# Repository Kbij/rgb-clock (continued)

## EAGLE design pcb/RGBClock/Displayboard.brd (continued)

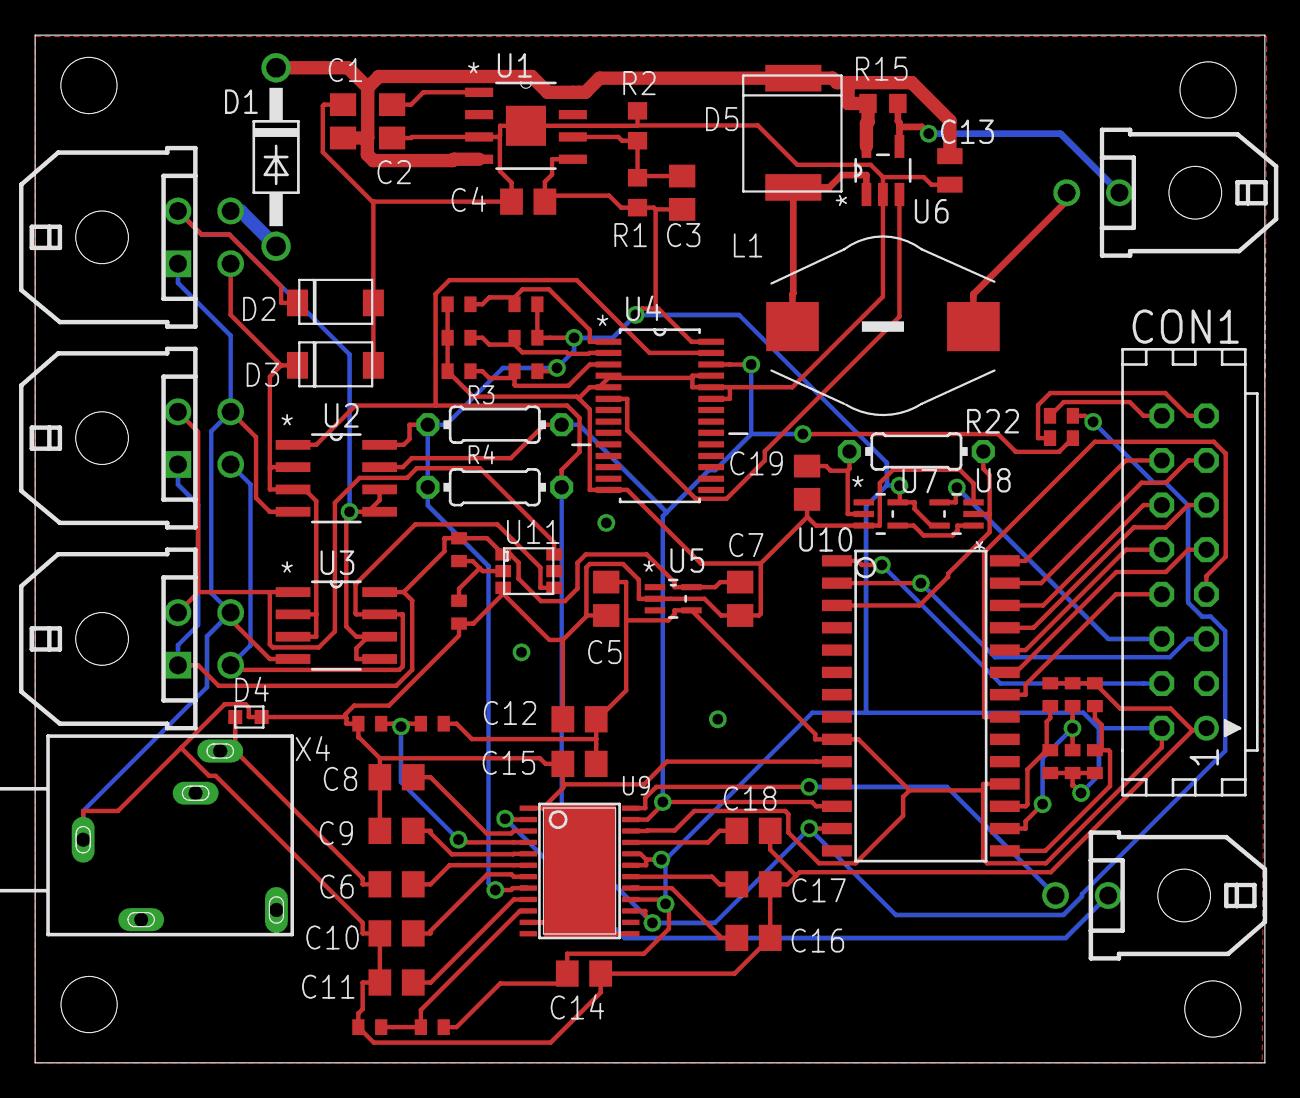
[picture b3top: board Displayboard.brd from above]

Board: 2 copper layers, 70.0 x 58.5 mm, 69 parts (0 on the bottom side), 53 nets.

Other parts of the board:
R27: A1-1; R0402
R28: A1-0; R0402
U9: TPA0172-HTSSOP24; HT-TSSOP-24
U10: MCP23017SO; SO28W
U11: TSL2561; TMB-6

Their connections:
+3V3: R27.2, U11.1; also elsewhere on the board
+5V: U9.8, U9.16, U9.19, U9.20, U9.22, U10.9, U10.18; also elsewhere on the board
D0: U10.21; also elsewhere on the board
D1: U10.22; also elsewhere on the board
D2: U10.23; also elsewhere on the board
D3: U10.24; also elsewhere on the board
D4: U10.25; also elsewhere on the board
D5: U10.26; also elsewhere on the board
D6: U10.27; also elsewhere on the board
D7: U10.28; also elsewhere on the board
GND: R28.1, U9.1, U9.11, U9.13, U9.HEATSINK, U10.10, U11.3; also elsewhere on the board
unnamed 13: U10.3; also elsewhere on the board
unnamed 14: U9.17; also elsewhere on the board
unnamed 15: U9.18; also elsewhere on the board
unnamed 17: U11.6; also elsewhere on the board
unnamed 19: U11.4; also elsewhere on the board
unnamed 21: U9.24; also elsewhere on the board
unnamed 22: U9.2; also elsewhere on the board
unnamed 23: U9.6; also elsewhere on the board
unnamed 24: U9.9; also elsewhere on the board
unnamed 25: U9.7; also elsewhere on the board
unnamed 26: U9.5; also elsewhere on the board
unnamed 27: U9.3; also elsewhere on the board
unnamed 28: U10.16; also elsewhere on the board
unnamed 29: U10.15; also elsewhere on the board
unnamed 31: U10.17; also elsewhere on the board
unnamed 33: U9.21; also elsewhere on the board
unnamed: R27.1, R28.2, U11.2
unnamed 44: U9.4; also elsewhere on the board
unnamed 45: U9.10; also elsewhere on the board
RS: U10.1; also elsewhere on the board
RW: U10.2; also elsewhere on the board
SCL: U9.23, U10.12; also elsewhere on the board
SDA: U9.15, U10.13; also elsewhere on the board

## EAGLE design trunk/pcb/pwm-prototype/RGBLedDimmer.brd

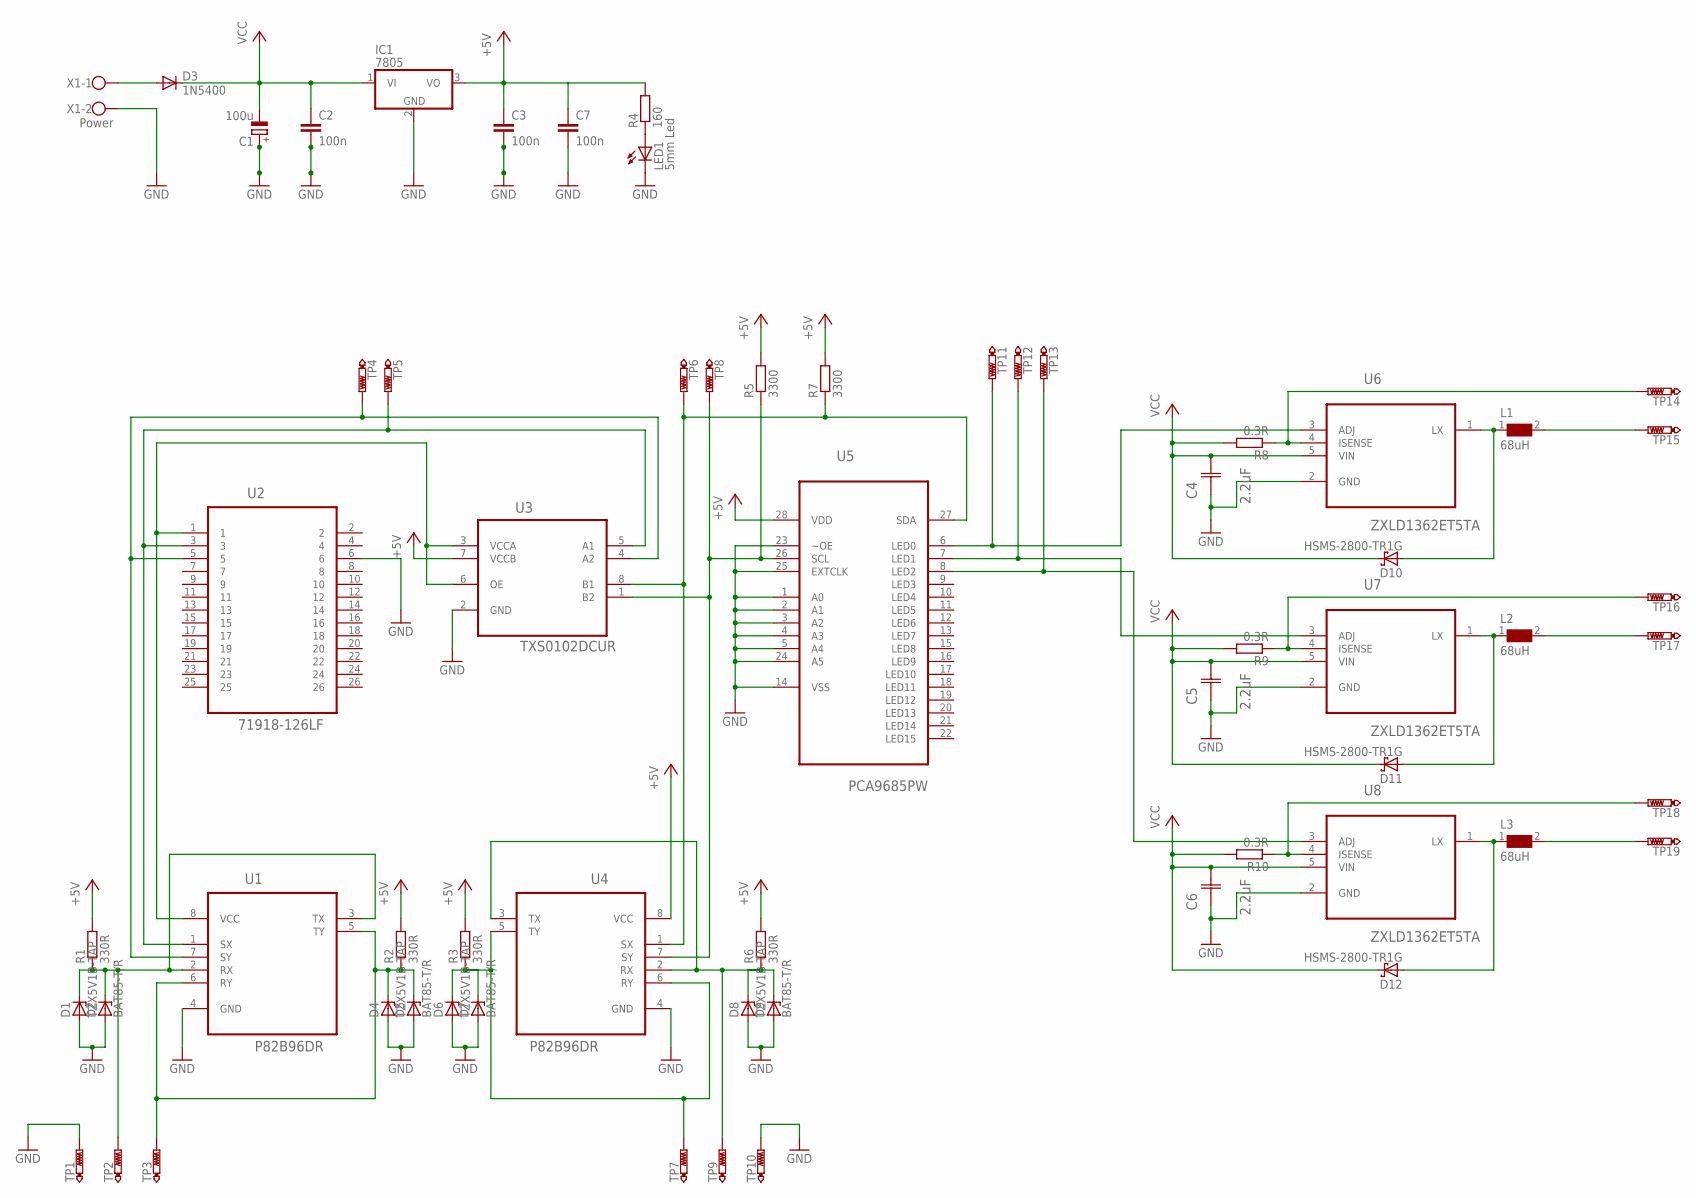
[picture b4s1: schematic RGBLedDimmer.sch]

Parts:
C1: 100u; E3,5-8
C2, C3, C7: 100n; C025_050-025X075
C4, C5, C6: 2.2uF; CAPC2013X152N
D1, D4, D6, D8: TZX5V1B-TAP; DO34Z7
D2, D5, D7, D9: BAT85-T/R; DO34Z7
D3: 1N5400; DO201-15
D10, D11, D12: HSMS-2800-TR1G; SOT23
IC1: 7805; TO220V
L1, L2, L3: 68uH; L
LED1: 5mm Led; LED5MM
R1, R2, R3, R6: 330R; 0204/7
R4: 160; 0204/7
R5, R7: 3300; 0204/7
R8, R9, R10: 0.3R; R0603
TP1, TP2, TP3, TP4, TP5, TP6, TP7, TP8, TP9, TP10, TP11, TP12, TP13, TP14, TP15, TP16, TP17, TP18, TP19: PTR1PAD1-13; P1-13
U1, U4: P82B96DR; SOIC127P600X175-8N
U2: 71918-126LF; FCI_71918-126LF
U3: TXS0102DCUR; SOP50P310X90-8N
U5: PCA9685PW; SOP65P640X110-28N
U6, U7, U8: ZXLD1362ET5TA; SOT95P270X145-5N
X1: Power; W237-102

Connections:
+5V: C3.1, C7.1, IC1.3 (VO), R1.2, R2.2, R3.2, R4.2, R5.2, R6.2, R7.2, U3.7 (VCCB), U4.8 (VCC), U5.28 (VDD)
GND: C1.+, C2.2, C3.2, C4.1 (C1), C5.1 (C1), C6.1 (C1), C7.2, D1.A, D2.A, D4.A, D5.A, D6.A, D7.A, D8.A, D9.A, IC1.2 (GND), LED1.K (C), TP1.TP, TP10.TP, U1.4 (GND), U2.6, U3.2 (GND), U4.4 (GND), U5.1 (A0), U5.2 (A1), U5.3 (A2), U5.4 (A3), U5.5 (A4), U5.14 (VSS), U5.23 (~OE), U5.24 (A5), U5.25 (EXTCLK), U6.2 (GND), U7.2 (GND), U8.2 (GND), X1.2
unnamed: R8.1, TP14.TP, U6.4 (ISENSE)
unnamed: TP12.TP, U5.7 (LED1), U7.3 (ADJ)
unnamed: R7.1, TP6.TP, U3.8 (B1), U4.1 (SX), U5.27 (SDA)
unnamed: R9.1, TP16.TP, U7.4 (ISENSE)
unnamed: L2.2, TP17.TP
unnamed: L1.2, TP15.TP
unnamed: U1.8 (VCC), U2.1, U3.3 (VCCA), U3.6 (OE)
unnamed: TP11.TP, U5.6 (LED0), U6.3 (ADJ)
unnamed: D11.1 (A), L2.1, U7.1 (LX)
unnamed: D10.1 (A), L1.1, U6.1 (LX)
unnamed: D3.A, X1.1
unnamed: R5.1, TP8.TP, U3.1 (B2), U4.7 (SY), U5.26 (SCL)
unnamed: TP5.TP, U1.1 (SX), U2.3, U3.5 (A1)
unnamed: TP4.TP, U1.7 (SY), U2.5, U3.4 (A2)
unnamed: TP13.TP, U5.8 (LED2), U8.3 (ADJ)
unnamed: R10.1, TP18.TP, U8.4 (ISENSE)
unnamed: D8.C, D9.C, R6.1, TP9.TP, U4.2 (RX), U4.3 (TX)
unnamed: L3.2, TP19.TP
unnamed: D12.1 (A), L3.1, U8.1 (LX)
unnamed: D1.C, D2.C, R1.1, TP2.TP, U1.2 (RX), U1.3 (TX)
unnamed: D4.C, D5.C, R2.1, TP3.TP, U1.5 (TY), U1.6 (RY)
unnamed: D6.C, D7.C, R3.1, TP7.TP, U4.5 (TY), U4.6 (RY)
unnamed: LED1.A, R4.1
VCC: C1.-, C2.1, C4.2 (C2), C5.2 (C2), C6.2 (C2), D3.C, D10.3 (C), D11.3 (C), D12.3 (C), IC1.1 (VI), R8.2, R9.2, R10.2, U6.5 (VIN), U7.5 (VIN), U8.5 (VIN)

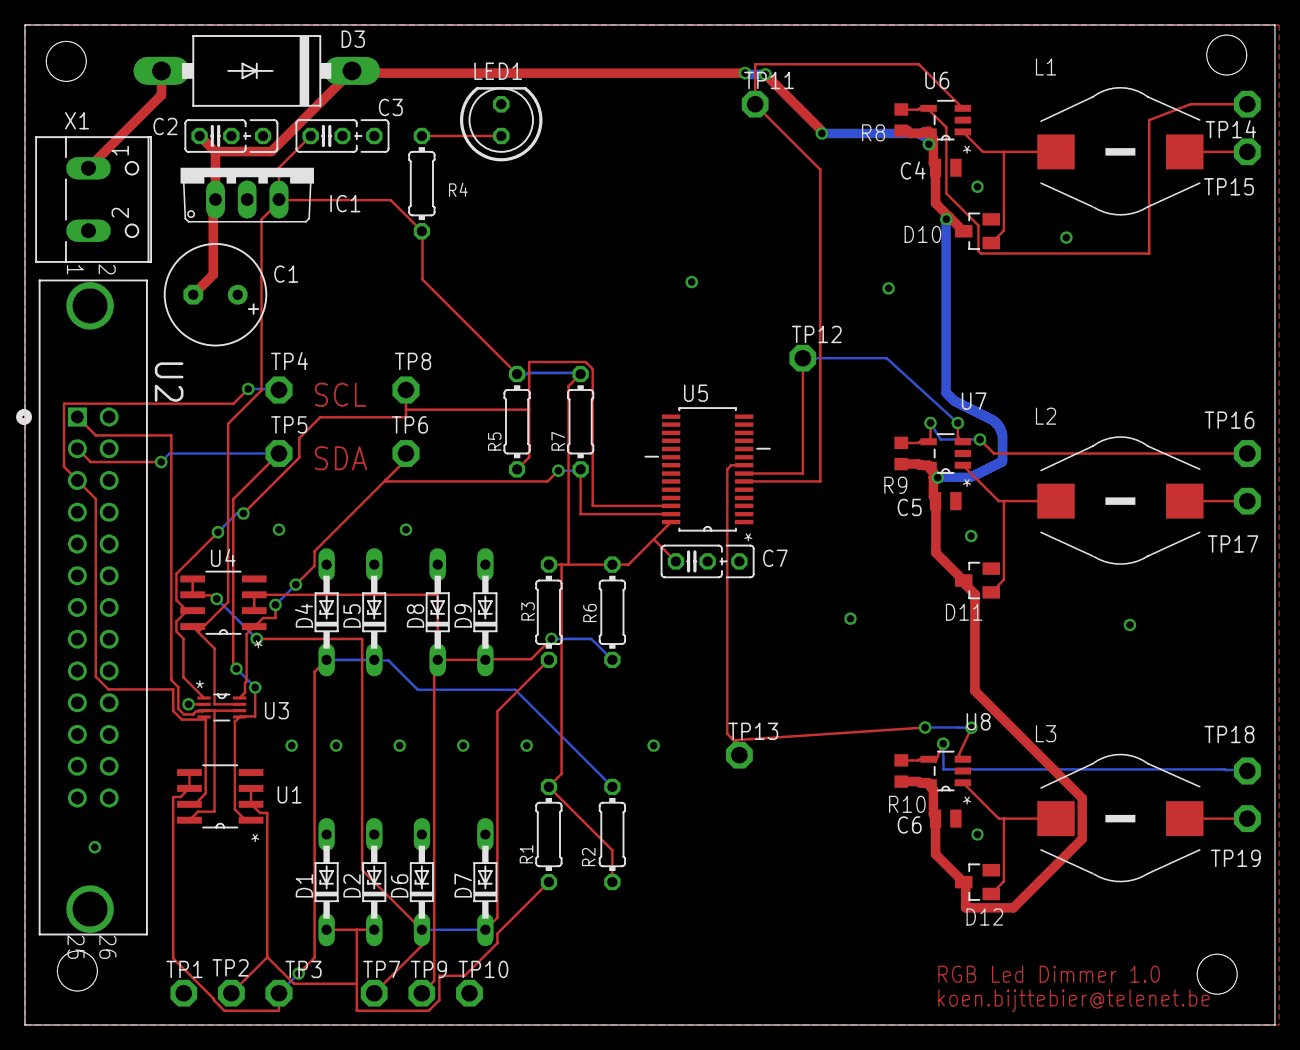
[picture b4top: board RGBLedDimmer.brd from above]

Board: 2 copper layers, 100.0 x 80.0 mm, 62 parts (0 on the bottom side), 26 nets.

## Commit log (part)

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2013-10-29 Mainboard + displayboard
2013-10-30 updating displayboard
2013-11-01 Mainboard, Displayboard, Leddriverboard
2013-11-06 Cleanup schematic
2013-11-08 Routing displayoard and cleanup board
2013-11-09 Led driver
2013-11-09 Export Gerber
2013-11-09 gerber panelize
2013-11-09 Panelizing to a big board ...
2013-11-09 adding 3D gerber viewer
2013-11-09 rename
2013-11-09 Beta version master pcb (not complete routed !)
2013-11-10 Just before freerouter
2013-11-10 Leddriver board complete
2013-11-11 Mainboard routable !
2013-11-11 Draft routerd mainboard
2013-11-11 board images
2013-11-11 Mainpanel Ready
2013-11-12 Final1
2013-11-13 Adding analog power and light sensor
2013-11-14 updating component packages
2013-11-17 Main and Display updated
2013-11-17 Onderdelen
2013-11-18 Ready
2013-11-19 Final 1
2013-11-20 PCB as ordered
2013-11-23 updated bom
2013-11-27 adding install instructions
2013-11-27 config exception
2013-11-30 mainboard control
2013-12-01 Adding software watchdog
2013-12-02 watchdog working/ autodetect units disabled
2013-12-02 ignore bin dir
2013-12-02 unused dir
2013-12-06 Testing mainbord: radio working !!
2013-12-11 pwd driver and backlight
2013-12-11 cleanup
2013-12-11 fix include
2013-12-11 mainboardcontrol
2013-12-20 Cleanup on exit main + lcd backlight ,etc...
2013-12-23 ontime error on address failure; no light sensor
2014-01-03 include xml config and alarm file in system service
2014-01-03 change keyboard layout
2014-01-03 add frequency to the systemconfig
2014-01-04 keyboard: up read all keys
2014-01-04 Adding keyboard as watchdogfeeder
2014-01-04 some cleanup
2014-01-05 clear display on exit
2014-01-05 read all 12 keys
2014-01-05 fix rtc problem
2014-01-05 probe i2c address before starting alarmclock & light
2014-01-06 fix for rtc read on startup
2014-01-06 light sensor added
2014-01-11 named threads
2014-01-12 init
2014-01-14 rtc logging + startup problem
2014-01-16 reading and writing rtc; first try
2014-01-16 don' rename main thread
2014-01-16 not compiling
2014-01-17 Update RTC driver; now without native hwclock support -> improved reliability
2014-01-17 read empty alarm file
2014-01-22 make compatible with prototype again
2014-01-22 move light
2014-01-22 move light to hardware namespace
2014-01-23 Refactor pwm driver
2014-01-24 cleaning up
2014-01-27 alarm time
2014-02-10 Last tweaks
2014-02-14 fix alarm calculation and change slowup time
2014-02-16 gridlines
2014-02-17 Missing feet
2014-02-17 met voet
2014-03-10 refactor I2C
2014-03-10 catch exception
2014-03-14 added dwa-131 driver and config files
2014-03-14 i2c error per address
2014-03-18 fork daemon before anything else
2014-03-19 fix refactor bug I2C
2014-03-23 ntp state, etc...
2014-03-24 update edit display
2014-03-24 add watchdog
2014-03-25 base case
2014-03-27 i2c with retry
2014-03-27 halfweg
2014-03-27 seperated
2014-03-31 verstuurde offerte
2014-04-01 Register adresses + keyboard timeout watchdog
2014-04-01 alarm calculation
2014-04-01 Register adresses
2014-04-11 longer timeout
2014-05-09 alarm sync
2014-06-11 RTC Change
2014-06-11 prepare for general alarmsnooze
2014-06-11 no more alarmsync
2014-06-11 global alarm sync
2014-06-18 Remove uneeded fonts
2014-06-18 change watchdog timeout
2014-06-22 remove extra logging
2014-06-27 fix RDS
2014-07-01 stop slowup when volume is touched
2014-07-08 project file
2014-09-15 rds fix
2014-11-17 valgrind issues
2014-11-18 fix alarms on sunday (Damn !)
2014-11-23 auto power off, needs mutexes
2014-11-23 fix cppcheck error
2014-11-23 cppcheck errors
2014-12-13 auto power off
2014-12-13 std unique ptr
2015-01-03 thread mutex
2015-01-03 project
2015-01-13 hw watchdog
2015-03-16 Migrating wiki contents from Google Code
2015-05-04 keyboard separated read and working thread
2015-05-12 Cleanedup Radio
2015-05-13 fix updown timer radio
2015-05-17 umask web
2015-10-12 auto cancel edit display
2016-01-08 build support
2016-01-08 cmake
2016-01-08 missing define
2016-09-16 avoid glitches in i2c; read a minimum of 2 keyboard events for a short press
2017-08-05 disable tinyxml, make cmake work
2017-08-05 tinyxml to tinyxml2
2017-08-05 use libraries from github
2017-08-05 bootstrap & main cmake file
2017-08-05 remove old project
2017-08-05 new directory structure
2017-08-05 library compiles
2017-08-05 builds again (cmake)
2017-08-06 rgblib eclipse project
2017-08-06 eclipse projects
2017-08-06 gtest
2017-08-08 build libraries for eclipse
2017-08-09 read config file
2017-08-10 Make alarmmanager testable
2017-08-16 read/write xml files with xml2
2017-08-16 write config file from unit test
2017-08-16 working alarm notify test
2017-09-06 build x86
2017-10-17 restructure + unit tests + onetimeLoud alarm
2017-10-17 arm toolchain
2017-10-17 toolchain
2017-10-18 toolchain file
2017-11-04 bootstrap with buiding all libs
2017-11-04 smooth/not smooth + build support
2017-11-04 fix bootstrap
2017-11-05 logging
2017-12-02 alarmmanager fix
2017-12-02 startup order
2017-12-02 dont use getppid
2017-12-03 systemd service file
2019-03-25 fix alarm off (short and long press)
2020-03-01 alle componenten naar mainboard.lbr
2020-03-01 all components on board
2020-03-02 dab+ partially routed
2020-03-03 dab routed manually
2020-03-03 dab routed
2020-03-03 lower clearance to 6mil
2020-03-07 juiste positie
2020-03-11 met kleiner kristal
2020-03-11 move dab
2020-03-11 routed
2020-03-11 As send to JCLPCB
2020-04-01 build sysroot libraries
2020-04-01 - build sysroot - add RgbTest to CMake
2020-04-01 -tinyxml2 static lib
2020-04-06 - Added base DAB Receiver
2020-04-06 -dab documentation -bom Mainboard.b#1 -small changes pcb
2020-04-07 - mainboard control is pointer - dab init - test for DABReceiver (not a real unit test)
2020-04-13 -powerup -hostload -toolchain
2020-04-13 -missing files
2020-04-15 -firmware load working - get frequency list working - tune frequency not working :-)
2020-04-20 Voor optimalisatie (v2.1)
2020-04-21 Ver 2.1; as send to jclpcb
2020-04-22 - utils test
2020-05-06 Mainboard 2.1
2020-05-08 - digirad status
2020-05-09 - Eureka !!!
2020-05-09 - Add extra Si4684 layer (low level hardware driver)
2020-05-09 - Add extra Si4684 layer: moving commands
2020-05-09 - DAB scan
2020-05-14 - DAB Scan - integrate in app - does not compile !!
2020-05-16 - get DAB Info - integrate in RgbClock - extra commands
2020-05-18 - get DAB Info, write to LCD - Rssi info
2020-05-31 as send to Jclpcb (ver 1.3)
2020-06-24 - writing flash seems to work (seems, not sure !!)
2020-06-24 - flash write with crc check (seems to work)
2020-08-23 - extra command and const
2020-10-23 Send to jclpcb
2020-11-07 - spi working - changes in flash writing/loading not verified !!
2020-11-13 - dab with spi working - flash not working
2020-11-18 - boot working - flash write/read not working
2020-12-02 - working with spi (fixed si486x reset in test)
2020-12-02 - fix missing file
2021-05-10 - as installed
2021-05-11 - cleanup - freq/service from config
2021-05-16 - arduino lcd driver
2021-05-16 - working, bug changing interrupt code
2021-05-17 - working, but stopping after some time
2021-05-17 - fixed i2c interrupt
2021-05-19 - added fastlcdisplay
2021-06-01 - some comments
2021-06-20 - working (with arduino i2c fix)
2021-06-20 - working
